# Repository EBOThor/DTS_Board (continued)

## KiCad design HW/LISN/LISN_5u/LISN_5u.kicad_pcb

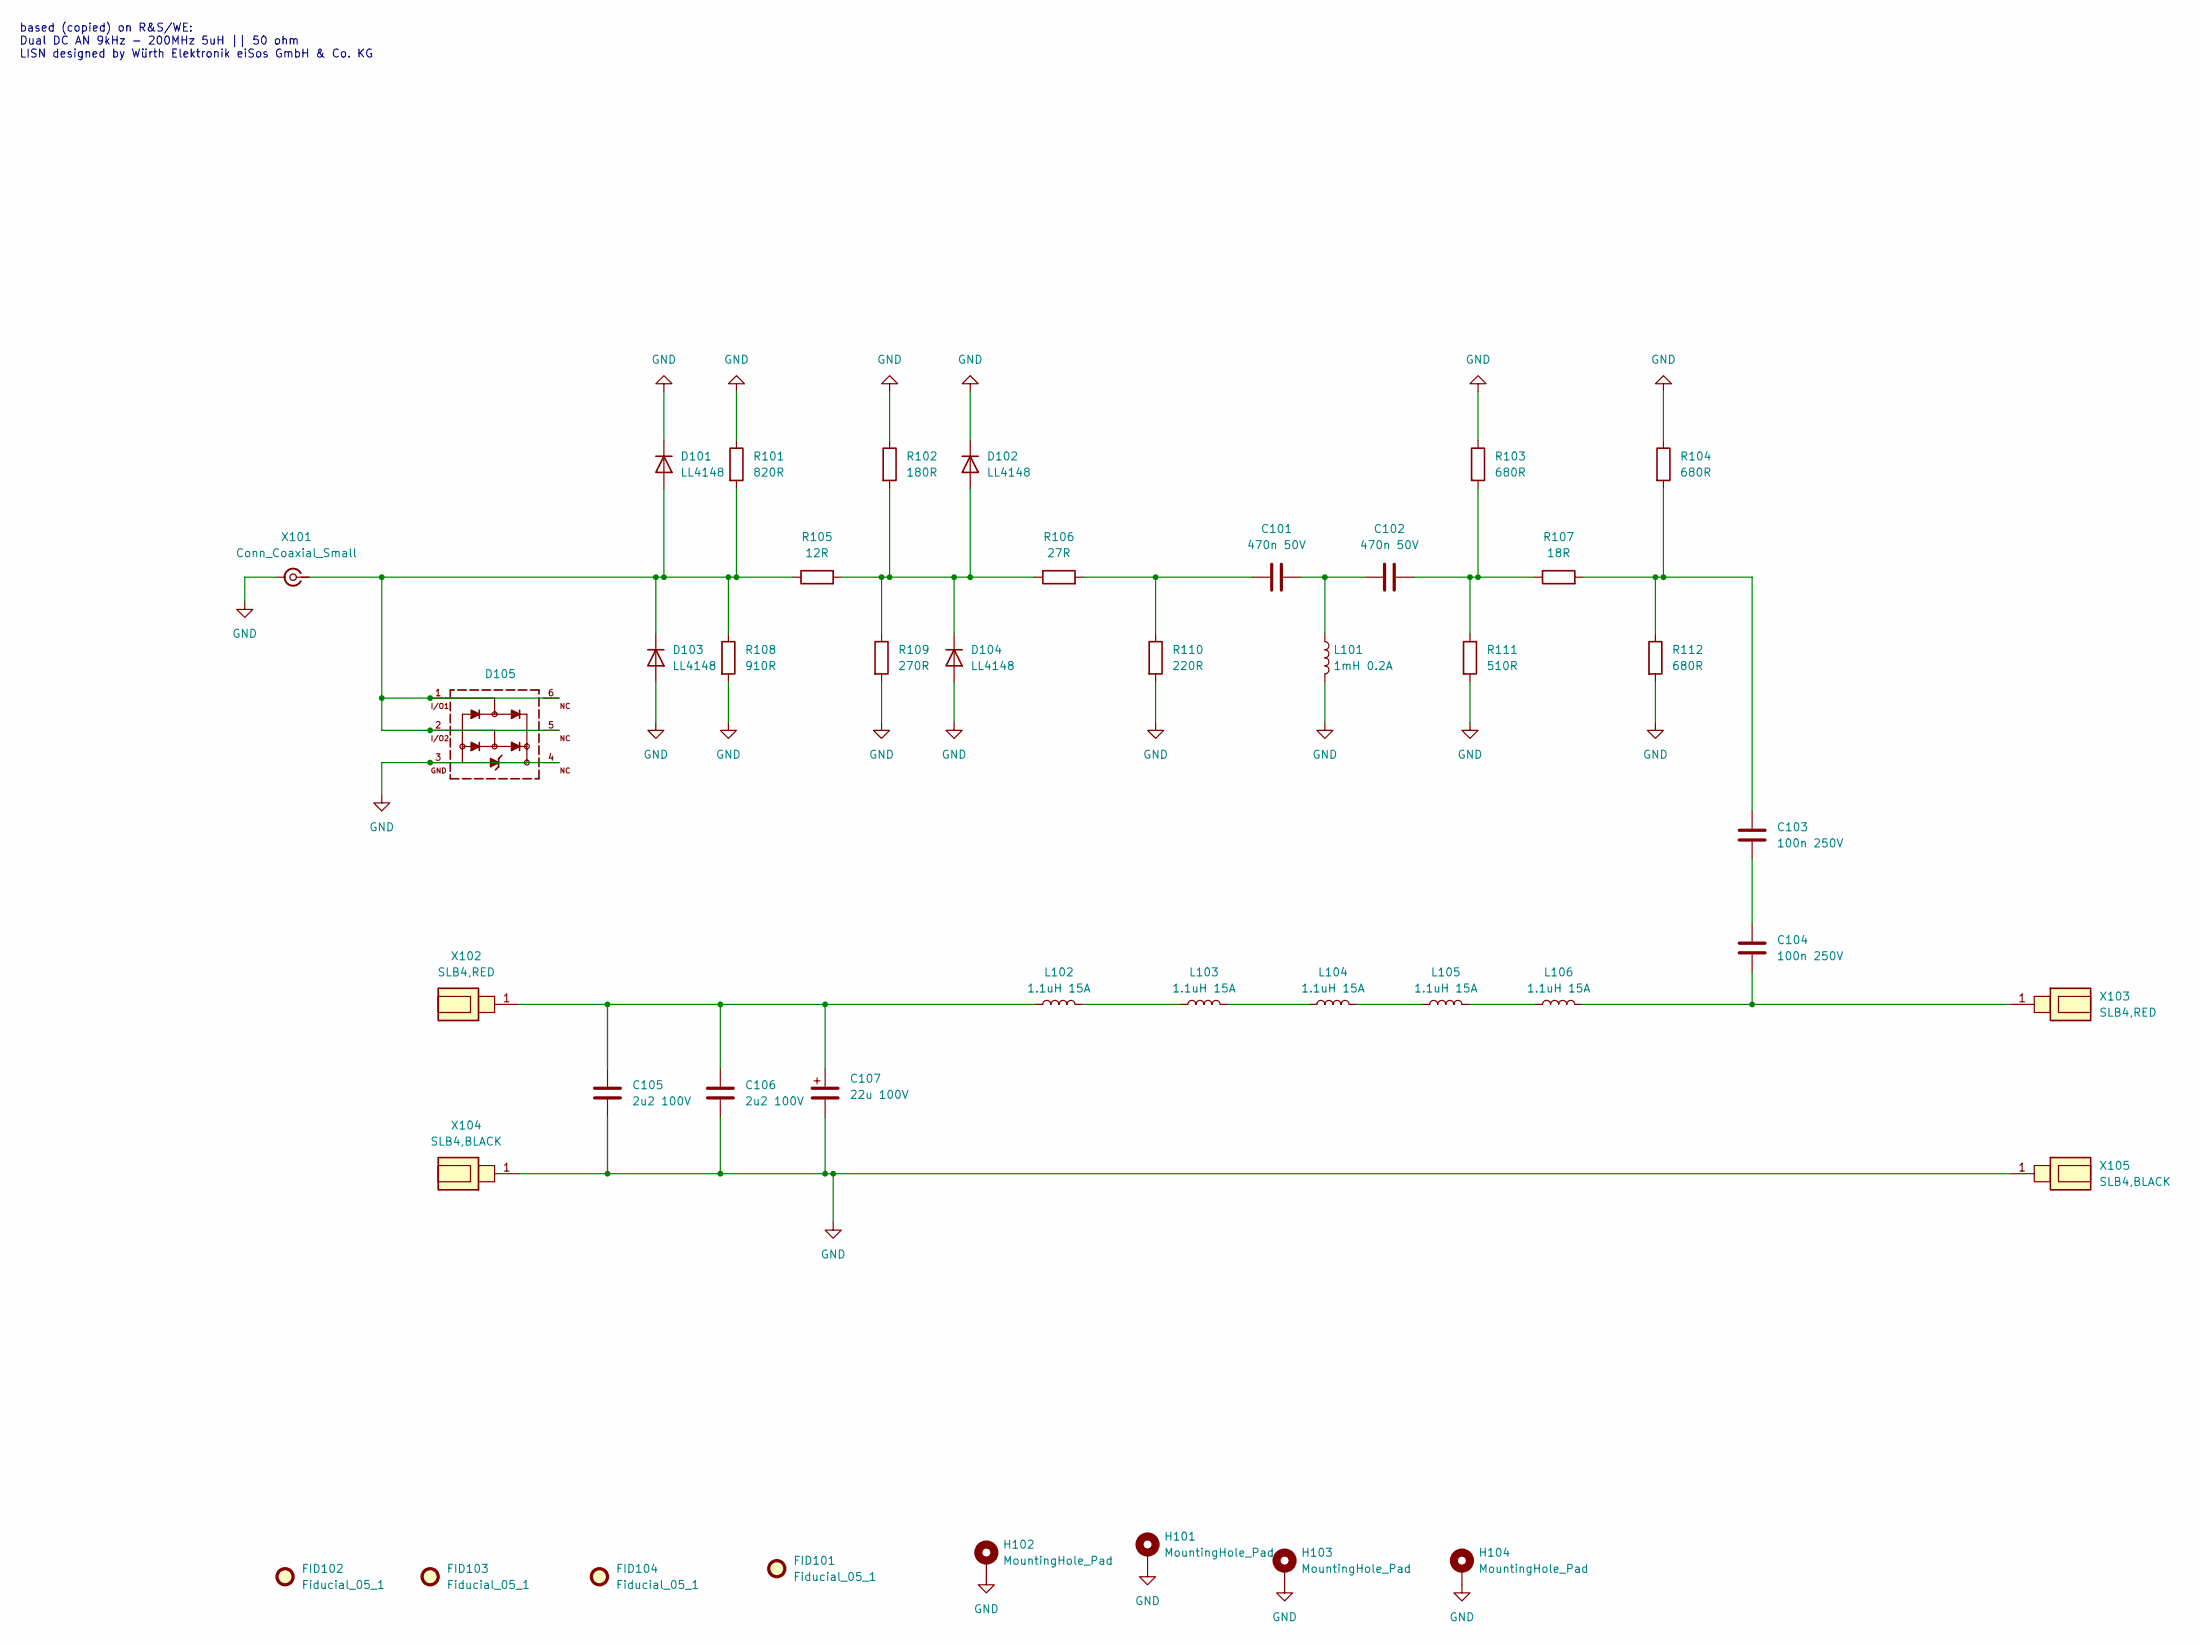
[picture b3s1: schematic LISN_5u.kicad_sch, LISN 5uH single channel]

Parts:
C101, C102: 470n 50V; C_0805_2012Metric; MPN C;C;T1;S;P0805;NA
C103, C104: 100n 250V; C_1206_3216Metric; MPN 885342208004
C105, C106: 2u2 100V; C_1210_3225Metric; MPN 885012209071
C107: 22u 100V; CP_Elec_8x10.5; MPN WE 865060853003
D101, D102, D103, D104: LL4148; D_MiniMELF; MPN LL4148
D105: 3.3Vdc; WE-TVS_DFN1210-6L; MPN 824012823
FID101, FID102, FID103, FID104: Fiducial_05_1; Fiducial_0.5mm_Mask1mm
H101, H102, H103, H104: MountingHole_Pad; MountingHole_3.2mm_M3_DIN965_Pad_TopBottom
L101: 1mH 0.2A; L_WE-LQS-5040; MPN WE 74404054102
L102, L103, L104, L105, L106: 1.1uH 15A; L_Wuerth_HCI-7050; MPN WE 744314110
R101: 820R; R_0603_1608Metric; MPN R;G;T1;S;P0603;NA
R102: 180R; R_0603_1608Metric; MPN R;G;T1;S;P0603;NA
R103, R104, R112: 680R; R_0603_1608Metric; MPN R;G;T1;S;P0603;NA
R105: 12R; R_0603_1608Metric; MPN R;G;T1;S;P0603;NA
R106: 27R; R_0603_1608Metric; MPN R;G;T1;S;P0603;NA
R107: 18R; R_0603_1608Metric; MPN R;G;T1;S;P0603;NA
R108: 910R; R_0603_1608Metric; MPN R;G;T1;S;P0603;NA
R109: 270R; R_0603_1608Metric; MPN R;G;T1;S;P0603;NA
R110: 220R; R_0603_1608Metric; MPN R;G;T1;S;P0603;NA
R111: 510R; R_0603_1608Metric; MPN R;G;T1;S;P0603;NA
X101: Conn_Coaxial_Small; SMA_Samtec_SMA-J-P-X-ST-EM1_EdgeMount
X102, X103: SLB4,RED; SLB4_6x6mm; MPN SLB4 Red
X104, X105: SLB4,BLACK; SLB4_6x6mm; MPN SLB4 Black

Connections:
GND: C105.2, C106.2, C107.2, D101.1 (K), D102.1 (K), D103.2 (A), D104.2 (A), D105.3, D105.4, H101.1, H102.1, H103.1, H104.1, L101.2, R101.1, R102.1, R103.1, R104.1, R108.2, R109.2, R110.2, R111.2, R112.2, X101.2 (Ext), X104.1, X105.1
unnamed: C101.1, R106.2, R110.1
unnamed: C101.2, C102.1, L101.1
unnamed: C102.2, R103.2, R107.1, R111.1
unnamed: C103.1, R104.2, R107.2, R112.1
unnamed: C103.2, C104.1
unnamed: D101.2 (A), D103.1 (K), D105.1, D105.2, D105.5, D105.6, R101.2, R105.1, R108.1, X101.1 (In)
unnamed: D102.2 (A), D104.1 (K), R102.2, R105.2, R106.1, R109.1
unnamed: L102.2, L103.1
unnamed: L103.2, L104.1
unnamed: L104.2, L105.1
unnamed: L105.2, L106.1
unnamed: C105.1, C106.1, C107.1, L102.1, X102.1
unnamed: C104.2, L106.2, X103.1

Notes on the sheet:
based (copied) on R&S/WE: Dual DC AN 9kHz - 200MHz 5uH || 50 ohm LISN designed by Würth Elektronik eiSos GmbH & Co. KG

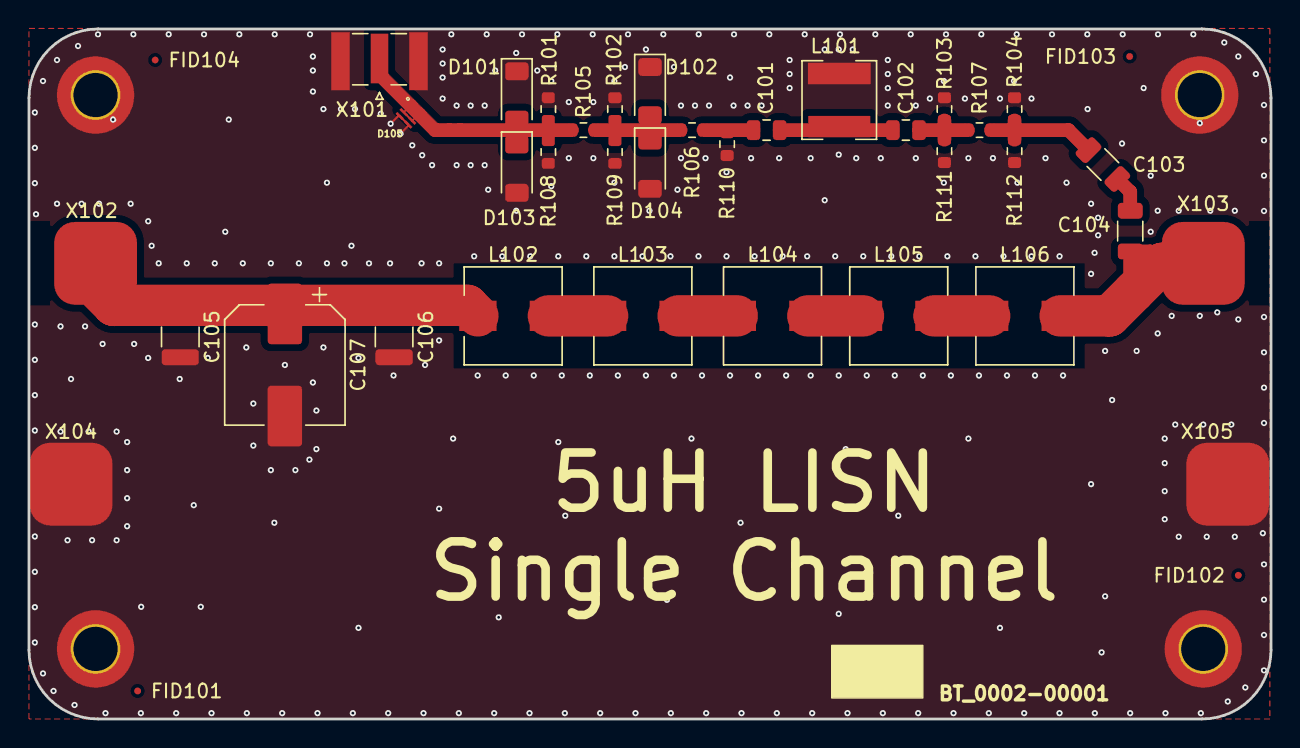
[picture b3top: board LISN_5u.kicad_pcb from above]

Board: 2 copper layers, 90.0 x 50.0 mm, 43 parts (0 on the bottom side), 14 nets.

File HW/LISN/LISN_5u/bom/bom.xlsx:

# | Qty | Value | Reference | Footprint | DNP | CPN | MPN | Description | digikey | mpn_new | cart | Column1 | Column2
1 | 2 | 470n 50V | C101,C102 | Capacitor_SMD:C_0805_2012Metric |  | BT00003-090680 | C;C;T1;S;P0805;NA | Capacitor | 732-7677-1-ND | WE 885012207102 | x | 2 | 4
2 | 2 | 100n 250V | C103,C104 | Capacitor_SMD:C_1206_3216Metric |  | BT00018-091000 | WE 885342208004 | Capacitor | 732-12118-1-ND | WE 885342208004 | x | 2 | 4
3 | 2 | 2u2 100V | C105,C106 | Capacitor_SMD:C_1210_3225Metric |  | BT00017-060022 | WE 885012209071 | Capacitor | 732-885012209071CT-ND | WE 885012209071 | x | 22 | 44
4 | 1 | 22u 100V | C107 | Capacitor_SMD:CP_Elec_8x10.5 |  | BT00019-060220 | WE 865060853003 | Capacitor | 732-865060853003CT-ND | WE 865060853003 | x | 9 | 9
5 | 4 | LL4148 | D101,D102,D103,D104 | Diode_SMD:D_MiniMELF |  | BT00020-00001 | LL4148 | 100V 0.15A standard switching diode, MiniMELF | LL4148FSCT-ND | LL4148 onsemi | x | 0.5 | 2
6 | 1 | 3.3Vdc | D105 | bt_footprints:WE-TVS_DFN1210-6L |  | BT09003-00001 | WE 824012823 | TVS 3v3 | 732-11794-1-ND | 824012823 | x | 6 | 6
7 | 1 | 1mH 0.2A | L101 | bt_footprints:L_WE-LQS-5040 |  | BT00203-00001 | WE 74404054102 | Inductor 1mH 0.2A 6 | 732-7254-1-ND | 74404054102 | x | 20 | 20
8 | 5 | 1.1uH 15A | L102,L103,L104,L105,L106 | Inductor_SMD:L_Wuerth_HCI-7050 |  | BT00202-00001 | WE 744314110 | Inductor 1.1uH 15A 3m | 732-1157-1-ND | 744314110 | x | 40 | 200
9 | 1 | 820R | R101 | Resistor_SMD:R_0603_1608Metric |  | BT00002-08200 | R;G;T1;S;P0603;NA | Resistor |  |  |  | 0.3 | 0.3
10 | 1 | 180R | R102 | Resistor_SMD:R_0603_1608Metric |  | BT00002-01800 | R;G;T1;S;P0603;NA | Resistor |  |  |  | 0.3 | 0.3
11 | 3 | 680R | R103,R104,R112 | Resistor_SMD:R_0603_1608Metric |  | BT00002-06800 | R;G;T1;S;P0603;NA | Resistor |  |  |  | 0.3 | 0.89999999999999991
12 | 1 | 12R | R105 | Resistor_SMD:R_0603_1608Metric |  | BT00002-00120 | R;G;T1;S;P0603;NA | Resistor |  |  |  | 0.3 | 0.3
13 | 1 | 27R | R106 | Resistor_SMD:R_0603_1608Metric |  | BT00002-00270 | R;G;T1;S;P0603;NA | Resistor |  |  |  | 0.3 | 0.3
14 | 1 | 18R | R107 | Resistor_SMD:R_0603_1608Metric |  | BT00002-00180 | R;G;T1;S;P0603;NA | Resistor |  |  |  | 0.3 | 0.3
15 | 1 | 910R | R108 | Resistor_SMD:R_0603_1608Metric |  | BT00002-09100 | R;G;T1;S;P0603;NA | Resistor |  |  |  | 0.3 | 0.3
16 | 1 | 270R | R109 | Resistor_SMD:R_0603_1608Metric |  | BT00002-02700 | R;G;T1;S;P0603;NA | Resistor |  |  |  | 0.3 | 0.3
17 | 1 | 220R | R110 | Resistor_SMD:R_0603_1608Metric |  | BT00002-02200 | R;G;T1;S;P0603;NA | Resistor |  |  |  | 0.3 | 0.3
18 | 1 | 510R | R111 | Resistor_SMD:R_0603_1608Metric |  | BT00002-05100 | R;G;T1;S;P0603;NA | Resistor |  |  |  | 0.3 | 0.3
19 | 1 | Conn_Coaxial_Small | X101 | Connector_Coaxial:SMA_Samtec_SMA-J-P-X-ST-EM1_EdgeMount |  |  |  | small coaxial connector (BNC, SMA, SMB, SMC, Cinch/RCA, LEMO, ...) | 732-13846-ND | WE 60312242114510 | x | 70 | 70
20 | 2 | SLB4,RED | X102,X103 | bt_footprints:SLB4_6x6mm |  | BT10008-00001 | SLB4 Red | SLB4 Red SMD |  |  |  | 0 | 0
21 | 2 | SLB4,BLACK | X104,X105 | bt_footprints:SLB4_6x6mm |  | BT10008-00002 | SLB4 Black | SLB4 BLACK SMD |  |  |  | 0 | 0
 |  |  |  |  |  |  |  |  |  |  |  |  | 362.60000000000008

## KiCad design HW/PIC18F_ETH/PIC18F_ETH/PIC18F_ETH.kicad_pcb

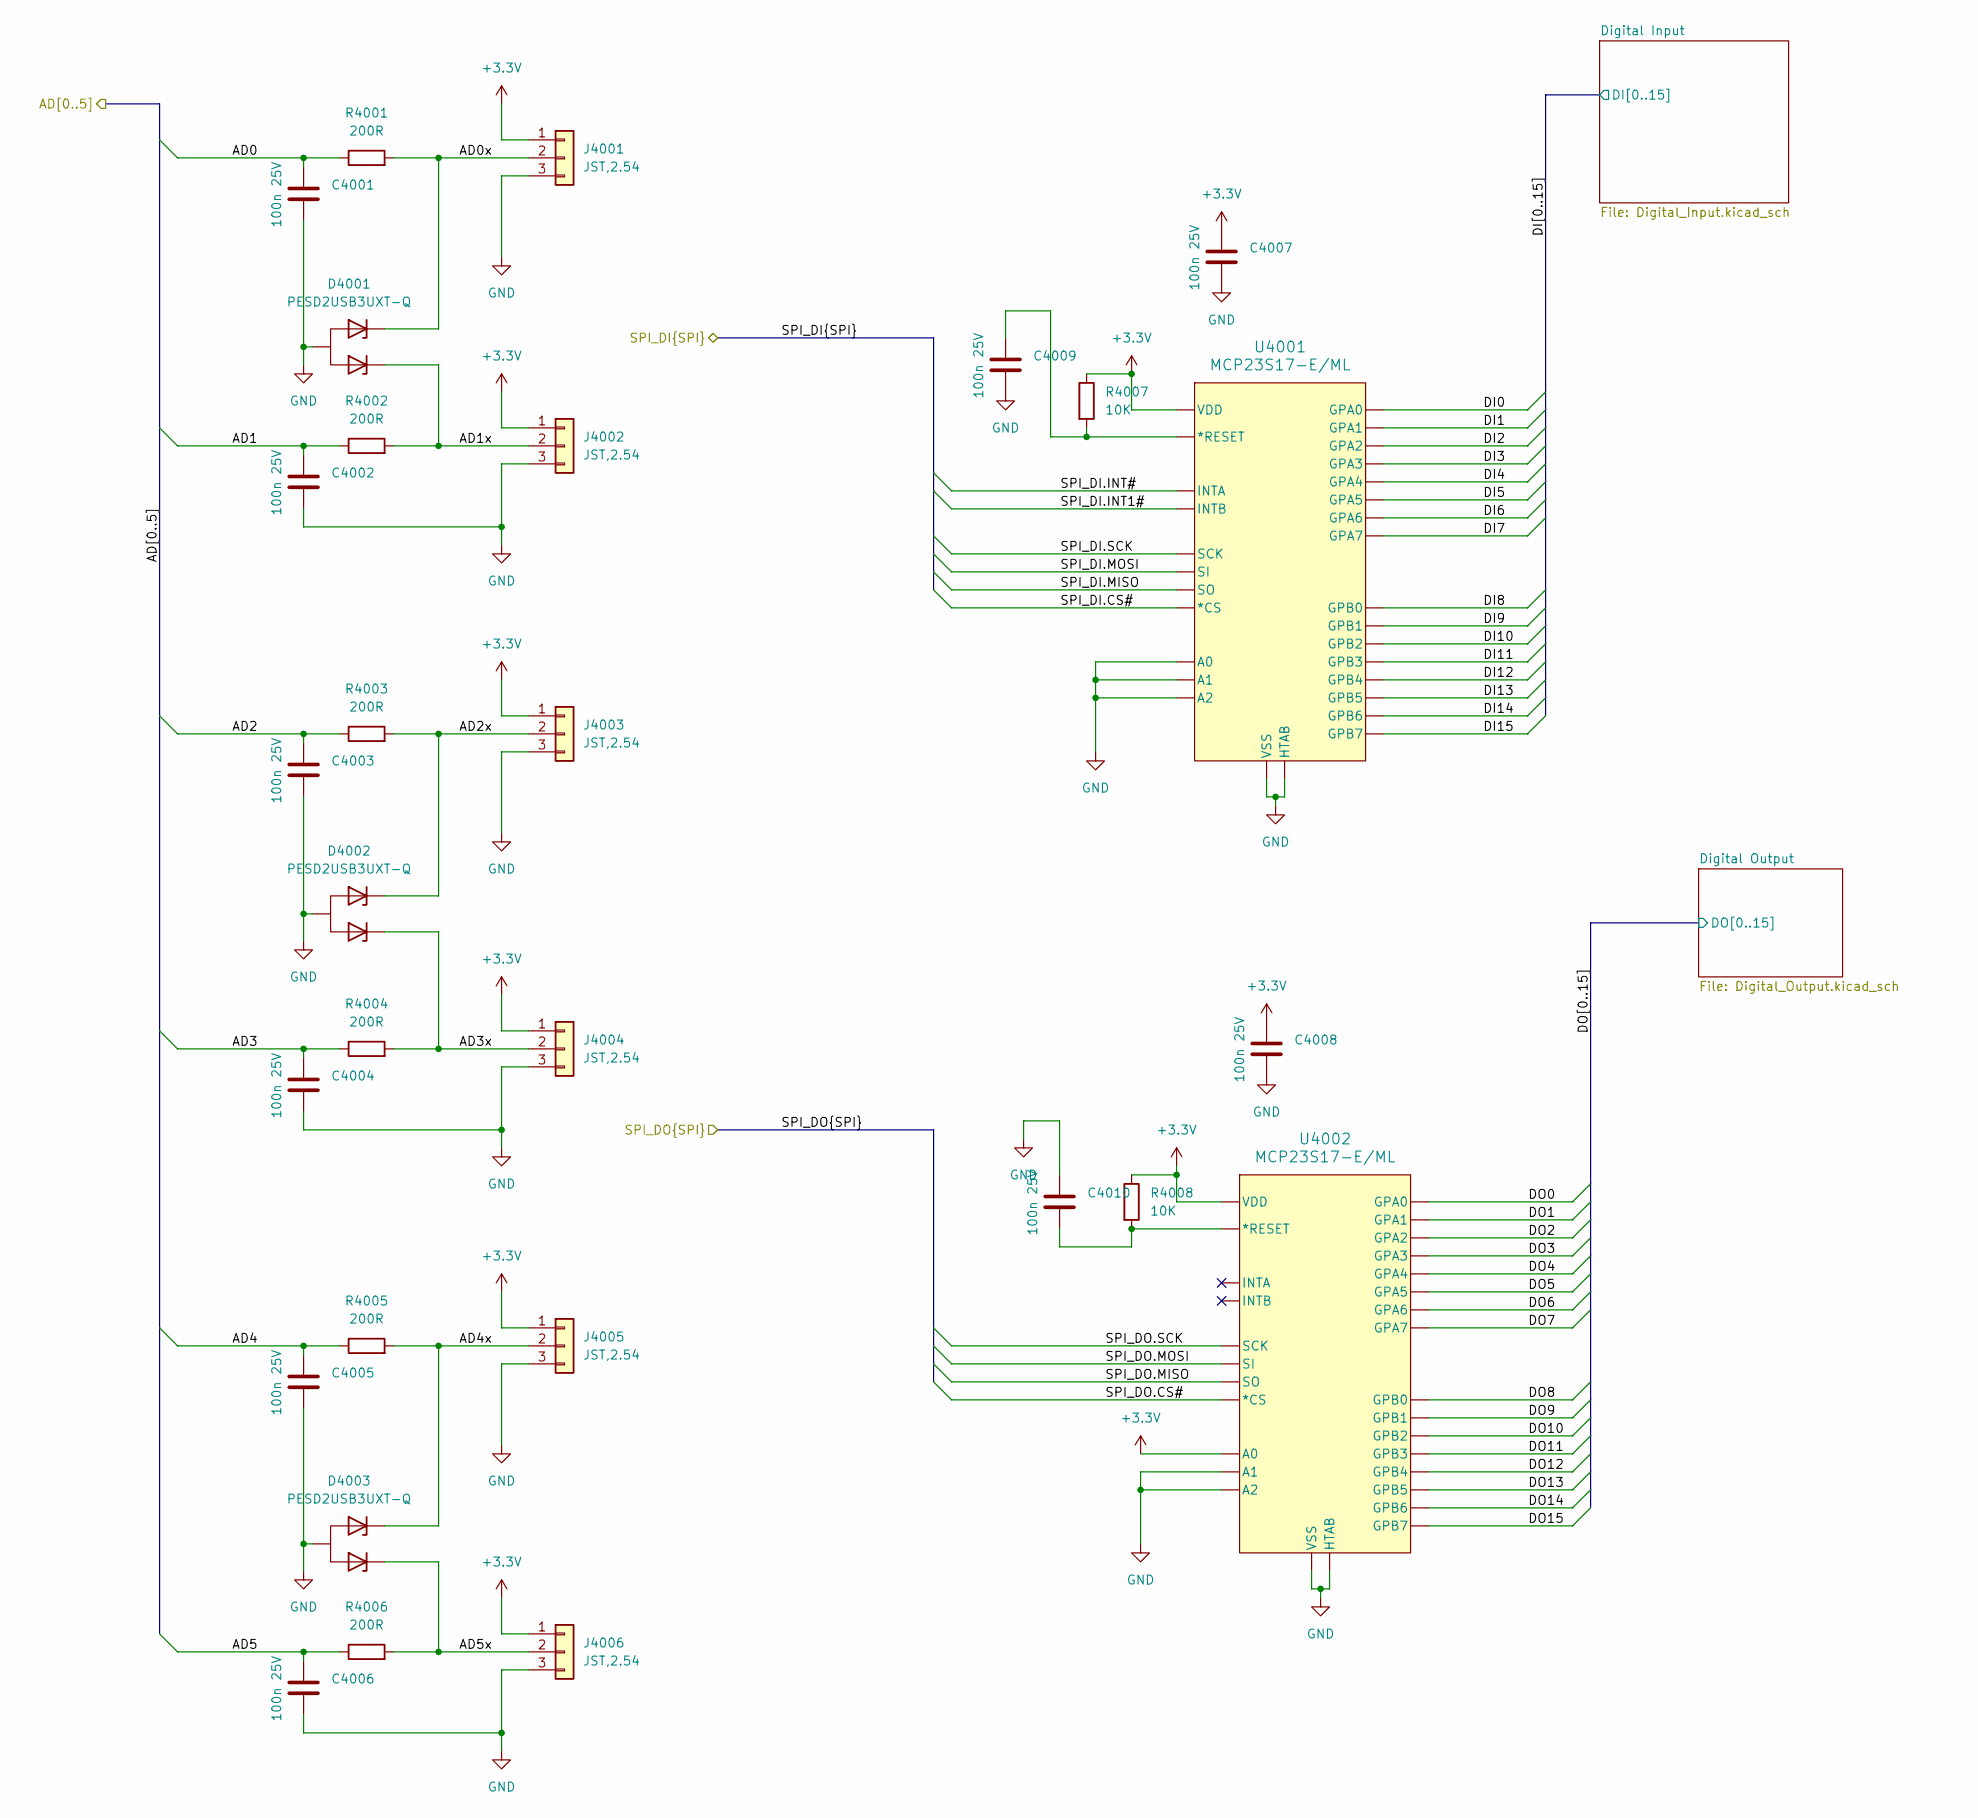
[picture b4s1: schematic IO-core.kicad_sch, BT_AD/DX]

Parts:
C4001, C4002, C4003, C4004, C4005, C4006, C4007, C4008, C4009, C4010: 100n 25V; C_0603_1608Metric; MPN C;C;T1;S;P0603;NA
D4001, D4002, D4003: PESD2USB3UXT-Q; SOT-23-3; MPN PESD2USB3UXT-Q
J4001, J4002, J4003, J4004, J4005, J4006: JST,2.54; JST_EH_B3B-EH-A_1x03_P2.50mm_Vertical; MPN JST 3 pin
R4001, R4002, R4003, R4004, R4005, R4006: 200R; R_0603_1608Metric; MPN R;G;T1;S;P0603;NA
R4007, R4008: 10K; R_0603_1608Metric; MPN R;G;T1;S;P0603;NA
U4001, U4002: MCP23S17-E/ML; QFN28_6x6MC_MCH; MPN MCP23S17-E_ML

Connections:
+3.3V: C4007.1, C4008.1, J4001.1, J4002.1, J4003.1, J4004.1, J4005.1, J4006.1, R4007.1, R4008.1, U4001.5 (VDD), U4002.5 (VDD), U4002.11 (A0); also elsewhere on the board
/AD0: C4001.1, R4001.1; also elsewhere on the board
/AD1: C4002.1, R4002.1; also elsewhere on the board
/AD2: C4003.1, R4003.1; also elsewhere on the board
/AD3: C4004.1, R4004.1; also elsewhere on the board
/AD4: C4005.1, R4005.1; also elsewhere on the board
/AD5: C4006.1, R4006.1; also elsewhere on the board
/IO_core/AD0x: D4001.2 (K2), J4001.2, R4001.2
/IO_core/AD1x: D4001.1 (K1), J4002.2, R4002.2
/IO_core/AD2x: D4002.2 (K2), J4003.2, R4003.2
/IO_core/AD3x: D4002.1 (K1), J4004.2, R4004.2
/IO_core/AD4x: D4003.2 (K2), J4005.2, R4005.2
/IO_core/AD5x: D4003.1 (K1), J4006.2, R4006.2
/IO_core/DI0: U4001.17 (GPA0); also elsewhere on the board
/IO_core/DI1: U4001.18 (GPA1); also elsewhere on the board
/IO_core/DI2: U4001.19 (GPA2); also elsewhere on the board
/IO_core/DI3: U4001.20 (GPA3); also elsewhere on the board
/IO_core/DI4: U4001.21 (GPA4); also elsewhere on the board
/IO_core/DI5: U4001.22 (GPA5); also elsewhere on the board
/IO_core/DI6: U4001.23 (GPA6); also elsewhere on the board
/IO_core/DI7: U4001.24 (GPA7); also elsewhere on the board
/IO_core/DI8: U4001.25 (GPB0); also elsewhere on the board
/IO_core/DI9: U4001.26 (GPB1); also elsewhere on the board
/IO_core/DI10: U4001.27 (GPB2); also elsewhere on the board
/IO_core/DI11: U4001.28 (GPB3); also elsewhere on the board
/IO_core/DI12: U4001.1 (GPB4); also elsewhere on the board
/IO_core/DI13: U4001.2 (GPB5); also elsewhere on the board
/IO_core/DI14: U4001.3 (GPB6); also elsewhere on the board
/IO_core/DI15: U4001.4 (GPB7); also elsewhere on the board
/IO_core/DO0: U4002.17 (GPA0); also elsewhere on the board
/IO_core/DO1: U4002.18 (GPA1); also elsewhere on the board
/IO_core/DO2: U4002.19 (GPA2); also elsewhere on the board
/IO_core/DO3: U4002.20 (GPA3); also elsewhere on the board
/IO_core/DO4: U4002.21 (GPA4); also elsewhere on the board
/IO_core/DO5: U4002.22 (GPA5); also elsewhere on the board
/IO_core/DO6: U4002.23 (GPA6); also elsewhere on the board
/IO_core/DO7: U4002.24 (GPA7); also elsewhere on the board
/IO_core/DO8: U4002.25 (GPB0); also elsewhere on the board
/IO_core/DO9: U4002.26 (GPB1); also elsewhere on the board
/IO_core/DO10: U4002.27 (GPB2); also elsewhere on the board
/IO_core/DO11: U4002.28 (GPB3); also elsewhere on the board
/IO_core/DO12: U4002.1 (GPB4); also elsewhere on the board
/IO_core/DO13: U4002.2 (GPB5); also elsewhere on the board
/IO_core/DO14: U4002.3 (GPB6); also elsewhere on the board
/IO_core/DO15: U4002.4 (GPB7); also elsewhere on the board
/SPI_DI.INT1#: U4001.15 (INTB); also elsewhere on the board
/SPI_DI.INT#: U4001.16 (INTA); also elsewhere on the board
/SPI_DO.CS#: U4001.7 (*CS), U4002.7 (*CS); also elsewhere on the board
/SPI_DO.MISO: U4001.10 (SO), U4002.10 (SO); also elsewhere on the board
/SPI_DO.MOSI: U4001.9 (SI), U4002.9 (SI); also elsewhere on the board
/SPI_DO.SCK: U4001.8 (SCK), U4002.8 (SCK); also elsewhere on the board
GND: C4001.2, C4002.2, C4003.2, C4004.2, C4005.2, C4006.2, C4007.2, C4008.2, C4009.2, C4010.1, D4001.3 (CA), D4002.3 (CA), D4003.3 (CA), J4001.3, J4002.3, J4003.3, J4004.3, J4005.3, J4006.3, U4001.6 (VSS), U4001.11 (A0), U4001.12 (A1), U4001.13 (A2), U4001.29 (HTAB), U4002.6 (VSS), U4002.12 (A1), U4002.13 (A2), U4002.29 (HTAB); also elsewhere on the board
unnamed: C4009.1, R4007.2, U4001.14 (*RESET)
unnamed: C4010.2, R4008.2, U4002.14 (*RESET)

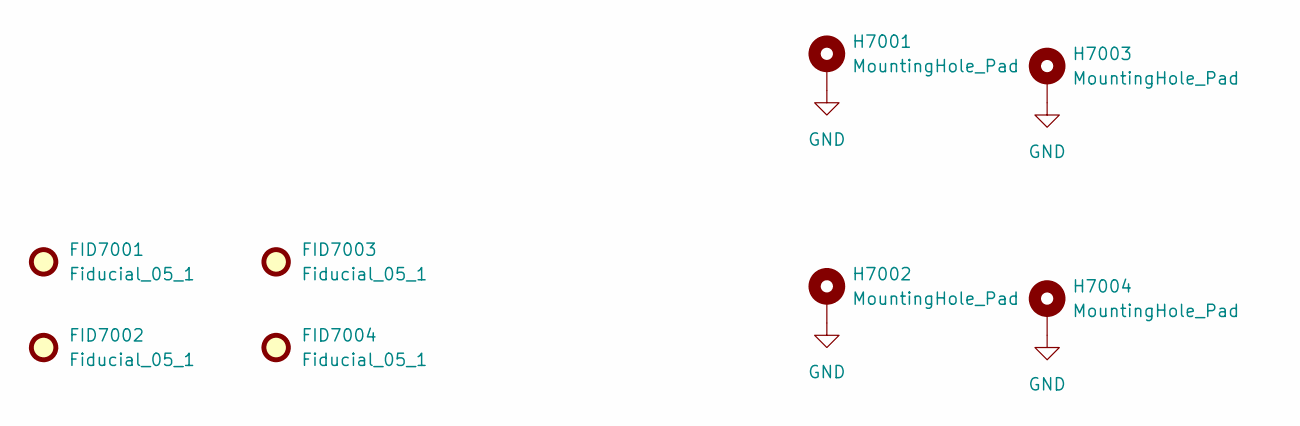
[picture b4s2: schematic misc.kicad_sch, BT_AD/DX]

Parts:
FID7001, FID7002, FID7003, FID7004: Fiducial_05_1; Fiducial_0.5mm_Mask1mm
H7001, H7002, H7003, H7004: MountingHole_Pad; MountingHole_3.2mm_M3_ISO7380_Pad

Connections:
GND: H7001.1, H7002.1, H7003.1, H7004.1; also elsewhere on the board

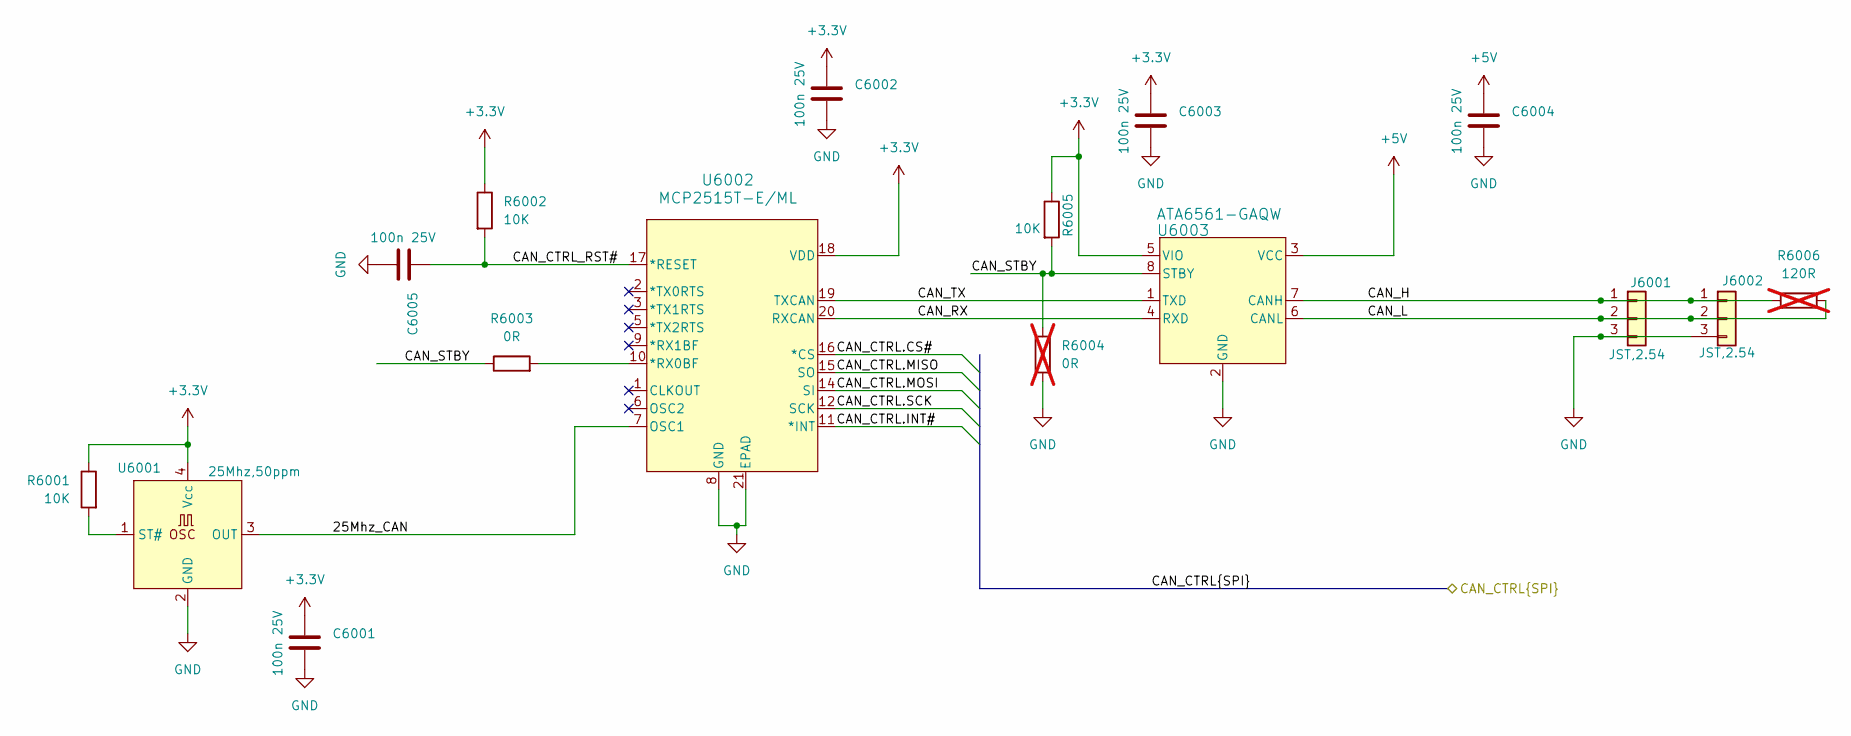
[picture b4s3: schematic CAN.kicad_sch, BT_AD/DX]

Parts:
C6001, C6002, C6003, C6004, C6005: 100n 25V; C_0603_1608Metric; MPN C;C;T1;S;P0603;NA
J6001, J6002: JST,2.54; JST_EH_B3B-EH-A_1x03_P2.50mm_Vertical; MPN JST 3 pin
R6001, R6002, R6005: 10K; R_0603_1608Metric; MPN R;G;T1;S;P0603;NA
R6003: 0R; R_0603_1608Metric; MPN R;G;T1;S;P0603;NA
R6004: 0R; R_0603_1608Metric; MPN R;G;T1;S;P0603;NA; not fitted
R6006: 120R; R_0603_1608Metric; MPN R;G;T1;S;P0603;NA; not fitted
U6001: 25Mhz,50ppm; Oscillator_SMD_SeikoEpson_SG8002CE-4Pin_3.2x2.5mm; MPN SG3225CAN 25.0000M-TJGA6
U6002: MCP2515T-E/ML; QFN20_4x4MC_MCH; MPN MCP2515T-E/ML
U6003: ATA6561-GAQW; SOIC8_4P9X3P9MC_MCH; MPN ATA6561-GAQW

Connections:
+3.3V: C6001.1, C6002.1, C6003.1, R6001.1, R6002.1, R6005.1, U6001.4 (Vcc), U6002.18 (VDD), U6003.5 (VIO); also elsewhere on the board
+5V: C6004.1, U6003.3 (VCC); also elsewhere on the board
/CAN/25Mhz_CAN: U6001.3 (OUT), U6002.7 (OSC1)
/CAN/CAN_CTRL_RST#: C6005.1, R6002.2, U6002.17 (*RESET)
/CAN/CAN_H: J6001.1, J6002.1, R6006.1, U6003.7 (CANH)
/CAN/CAN_L: J6001.2, J6002.2, R6006.2, U6003.6 (CANL)
/CAN/CAN_RX: U6002.20 (RXCAN), U6003.4 (RXD)
/CAN/CAN_STBY: R6003.1, R6004.2, R6005.2, U6003.8 (STBY)
/CAN/CAN_TX: U6002.19 (TXCAN), U6003.1 (TXD)
/CAN_CTRL.CS#: U6002.16 (*CS); also elsewhere on the board
/CAN_CTRL.INT#: U6002.11 (*INT); also elsewhere on the board
/SPI_DO.MISO: U6002.15 (SO); also elsewhere on the board
/SPI_DO.MOSI: U6002.14 (SI); also elsewhere on the board
/SPI_DO.SCK: U6002.12 (SCK); also elsewhere on the board
GND: C6001.2, C6002.2, C6003.2, C6004.2, C6005.2, J6001.3, J6002.3, R6004.1, U6001.2 (GND), U6002.8 (GND), U6002.21 (EPAD), U6003.2 (GND); also elsewhere on the board
unnamed: R6001.2, U6001.1 (ST#)
unnamed: R6003.2, U6002.10 (*RX0BF)

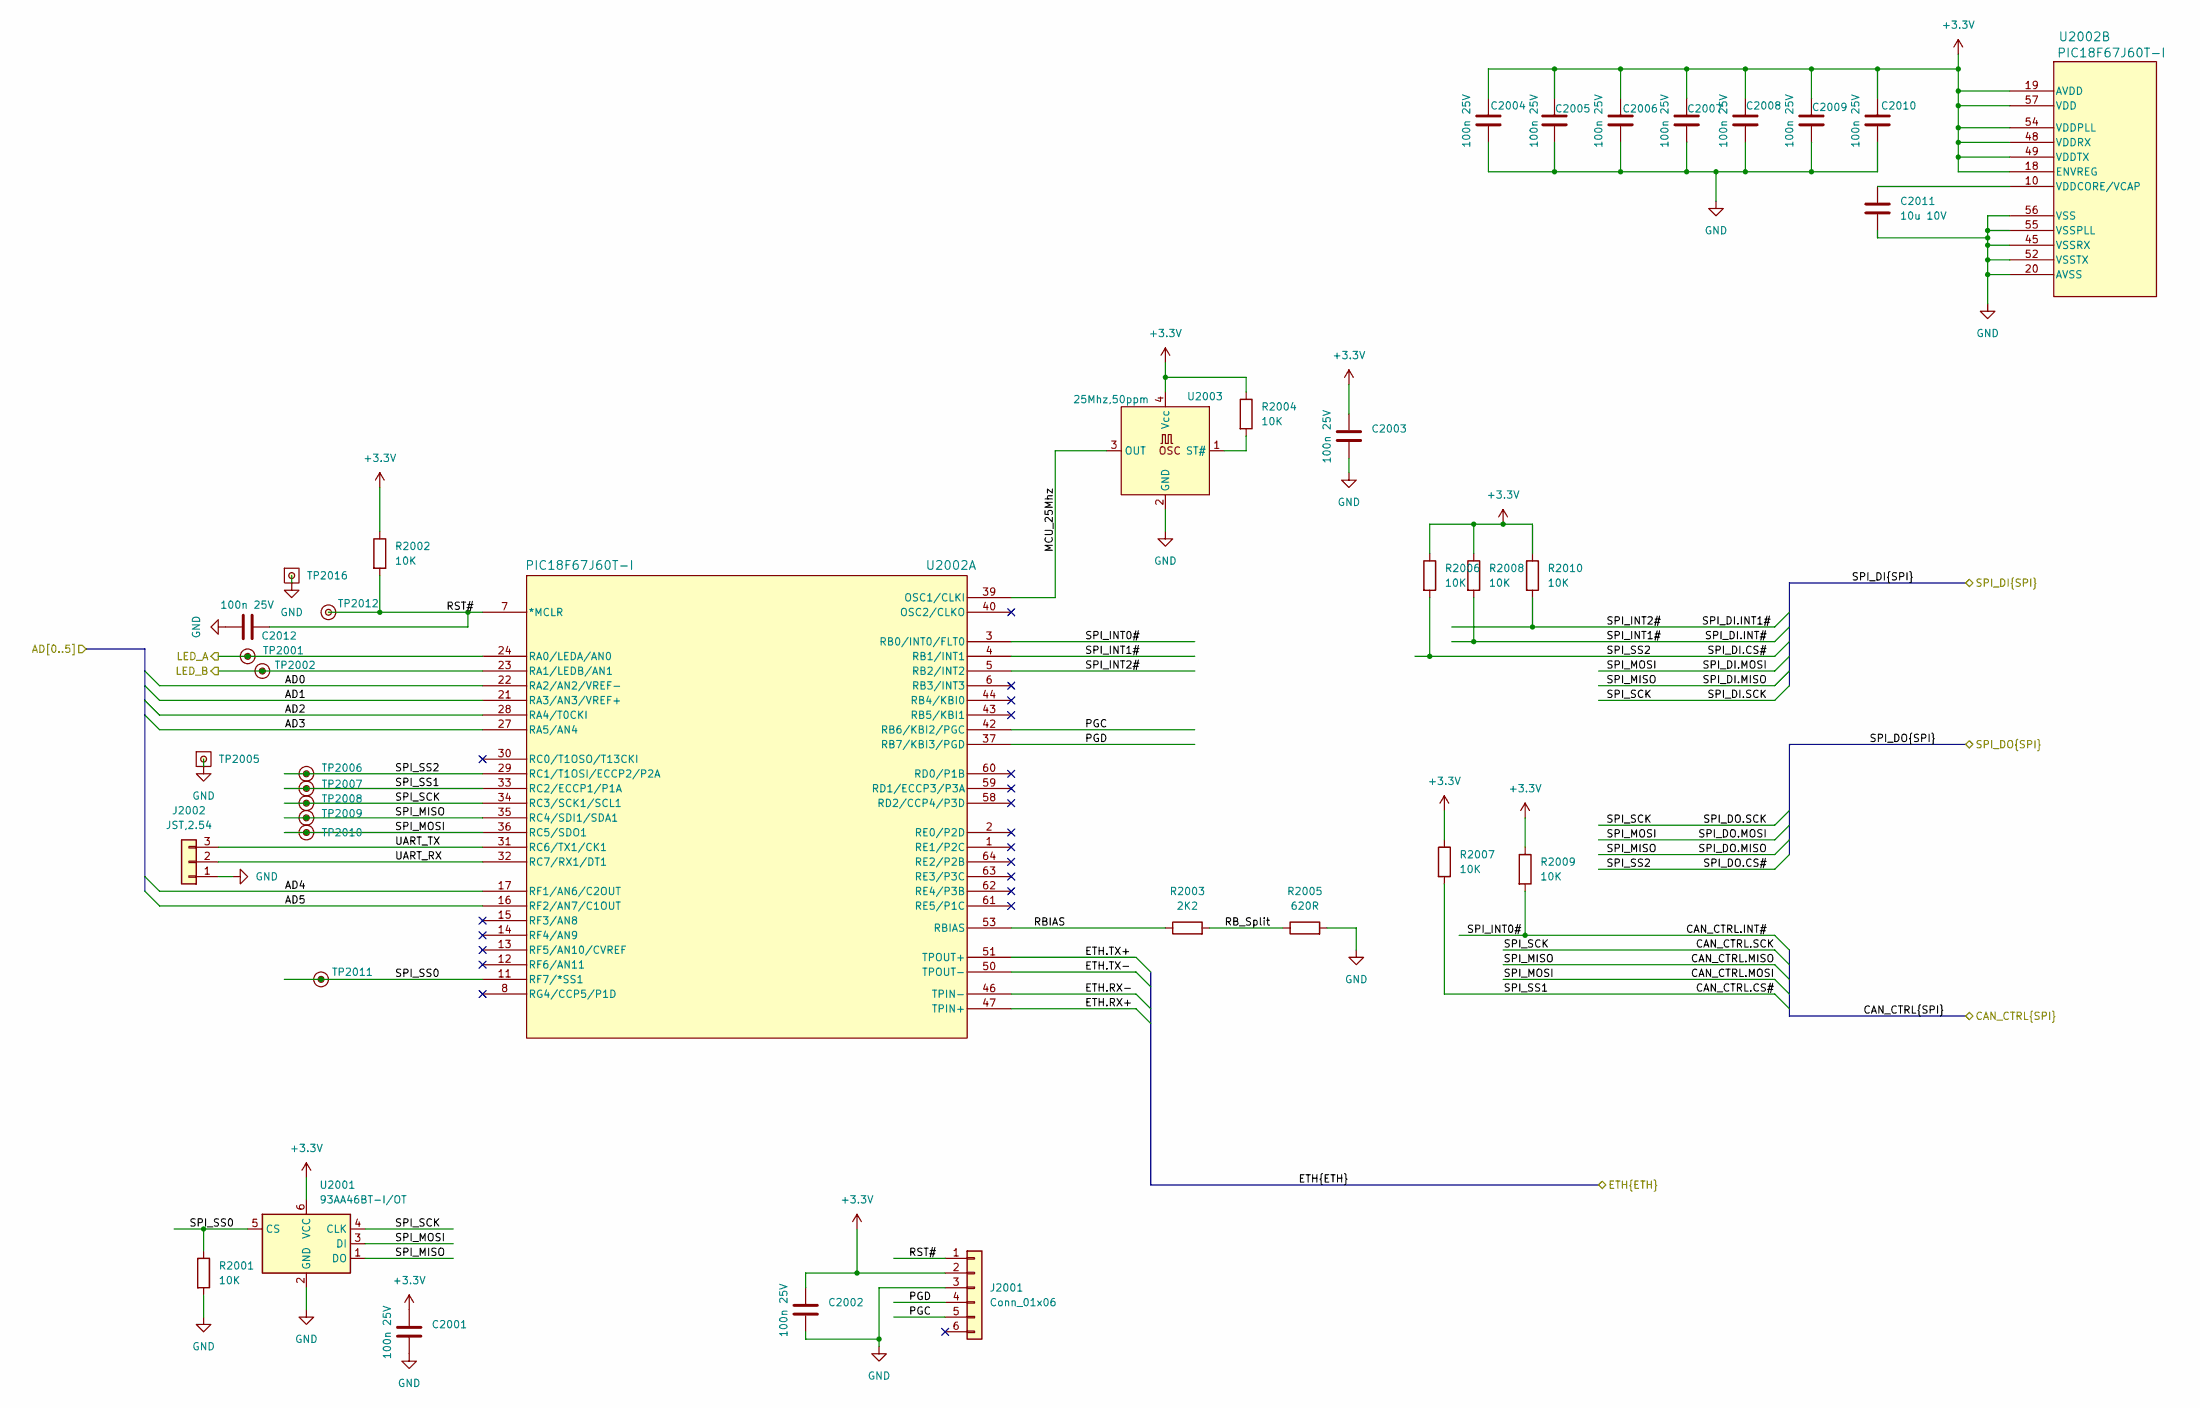
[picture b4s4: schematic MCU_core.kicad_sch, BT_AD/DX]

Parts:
C2001, C2002, C2003, C2004, C2005, C2006, C2007, C2008, C2009, C2010, C2012: 100n 25V; C_0603_1608Metric; MPN C;C;T1;S;P0603;NA
C2011: 10u 10V; C_0603_1608Metric; MPN C;C;T1;S;P0603;NA
J2001: Conn_01x06; PinHeader_1x06_P2.54mm_Vertical
J2002: JST,2.54; JST_EH_B3B-EH-A_1x03_P2.50mm_Vertical; MPN JST 3 pin
R2001, R2002, R2004, R2006, R2007, R2008, R2009, R2010: 10K; R_0603_1608Metric; MPN R;G;T1;S;P0603;NA
R2003: 2K2; R_0603_1608Metric; MPN R;G;T1;S;P0603;NA
R2005: 620R; R_0603_1608Metric; MPN R;G;T1;S;P0603;NA
TP2001, TP2002, TP2006, TP2007, TP2008, TP2009, TP2010, TP2011, TP2012: TestPoint; TestPoint_THTPad_D1.0mm_Drill0.5mm
TP2005, TP2016: TestPoint; TestPoint_THTPad_1.0x1.0mm_Drill0.5mm
U2001: 93AA46BT-I/OT; SOT-23-6; MPN 93AA46BT-I/OT
U2002: PIC18F67J60T-I; TQFP64_10x10MC_MCH; MPN PIC18F67J60T-I/PT
U2003: 25Mhz,50ppm; Oscillator_SMD_SeikoEpson_SG8002CE-4Pin_3.2x2.5mm; MPN SG3225CAN 25.0000M-TJGA6

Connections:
+3.3V: C2001.1, C2002.1, C2003.1, C2004.1, C2005.1, C2006.1, C2007.1, C2008.1, C2009.1, C2010.1, J2001.2, R2002.1, R2004.1, R2006.1, R2007.1, R2008.1, R2009.1, R2010.1, U2001.6 (VCC), U2002.18 (ENVREG), U2002.19 (AVDD), U2002.26 (VDD), U2002.38 (VDD), U2002.48 (VDDRX), U2002.49 (VDDTX), U2002.54 (VDDPLL), U2002.57 (VDD), U2003.4 (Vcc); also elsewhere on the board
/AD0: U2002.22 (RA2/AN2/VREF-); also elsewhere on the board
/AD1: U2002.21 (RA3/AN3/VREF+); also elsewhere on the board
/AD2: U2002.28 (RA4/T0CKI); also elsewhere on the board
/AD3: U2002.27 (RA5/AN4); also elsewhere on the board
/AD4: U2002.17 (RF1/AN6/C2OUT); also elsewhere on the board
/AD5: U2002.16 (RF2/AN7/C1OUT); also elsewhere on the board
/CAN_CTRL.CS#: R2007.2, TP2007.1, U2002.33 (RC2/ECCP1/P1A); also elsewhere on the board
/CAN_CTRL.INT#: R2009.2, U2002.3 (RB0/INT0/FLT0); also elsewhere on the board
/ETH_Connector/ETH.RX+: U2002.47 (TPIN+); also elsewhere on the board
/ETH_Connector/ETH.RX-: U2002.46 (TPIN-); also elsewhere on the board
/ETH_Connector/ETH.TX+: U2002.51 (TPOUT+); also elsewhere on the board
/ETH_Connector/ETH.TX-: U2002.50 (TPOUT-); also elsewhere on the board
/LED_G: TP2001.1, U2002.24 (RA0/LEDA/AN0); also elsewhere on the board
/LED_Y: TP2002.1, U2002.23 (RA1/LEDB/AN1); also elsewhere on the board
/MCU_core/MCU_25Mhz: U2002.39 (OSC1/CLKI), U2003.3 (OUT)
/MCU_core/PGC: J2001.5, U2002.42 (RB6/KBI2/PGC)
/MCU_core/PGD: J2001.4, U2002.37 (RB7/KBI3/PGD)
/MCU_core/RBIAS: R2003.1, U2002.53 (RBIAS)
/MCU_core/RB_Split: R2003.2, R2005.1
/MCU_core/RST#: C2012.1, J2001.1, R2002.2, TP2012.1, U2002.7 (*MCLR)
/MCU_core/SPI_SS0: R2001.1, TP2011.1, U2001.5 (CS), U2002.11 (RF7/*SS1)
/MCU_core/UART_RX: J2002.2, U2002.32 (RC7/RX1/DT1)
/MCU_core/UART_TX: J2002.3, U2002.31 (RC6/TX1/CK1)
/SPI_DI.INT1#: R2010.2, U2002.5 (RB2/INT2); also elsewhere on the board
/SPI_DI.INT#: R2008.2, U2002.4 (RB1/INT1); also elsewhere on the board
/SPI_DO.CS#: R2006.2, TP2006.1, U2002.29 (RC1/T1OSI/ECCP2/P2A); also elsewhere on the board
/SPI_DO.MISO: TP2009.1, U2001.1 (DO), U2002.35 (RC4/SDI1/SDA1); also elsewhere on the board
/SPI_DO.MOSI: TP2010.1, U2001.3 (DI), U2002.36 (RC5/SDO1); also elsewhere on the board
/SPI_DO.SCK: TP2008.1, U2001.4 (CLK), U2002.34 (RC3/SCK1/SCL1); also elsewhere on the board
GND: C2001.2, C2002.2, C2003.2, C2004.2, C2005.2, C2006.2, C2007.2, C2008.2, C2009.2, C2010.2, C2011.2, C2012.2, J2001.3, J2002.1, R2001.2, R2005.2, TP2005.1, TP2016.1, U2001.2 (GND), U2002.9 (VSS), U2002.20 (AVSS), U2002.25 (VSS), U2002.41 (VSS), U2002.45 (VSSRX), U2002.52 (VSSTX), U2002.55 (VSSPLL), U2002.56 (VSS), U2003.2 (GND); also elsewhere on the board
unnamed: C2011.1, U2002.10 (VDDCORE/VCAP)
unnamed: R2004.2, U2003.1 (ST#)
